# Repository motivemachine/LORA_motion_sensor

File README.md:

# LoRa Motion sensor
These are the kicad PCB and software files for the LoRa motion sensor, a wireless proximity alarm using the RCWL-0516 sensor and SX1278 radio. PCB designed in Kicad 5.1. The cache should contain all custom footprints. Handheld receiver design coming soon.

### Dependencies
Only dependency is the LoRa radio library by [Sandeep Mistry](https://github.com/sandeepmistry/arduino-LoRa), included in _/firmware/lib/_

### Software usage
Software was created and compiled with PlatformIO, but is usable by any arduino compatible IDE by compiling the program located in _/firmware/src_ as an arduino pro mini 3.3v/8mhz. Upload is done over ISP header. Be careful that programming signals are 3.3 volts, as the LoRa radio is not 5v tolerant.

### Using the device
Simply turn it on and place in an area you'd like to monitor. Choke points are best, such as near a gate, pathway, doorway or vehicle. The sensor works by detecting a phase change in it's 3Ghz oscillator and waking up the processor and radio, then sending the packet 'MOT' via LoRa radio protocol, along with packet and radio ID number.

Sensor range is about 20-30ft out the front and back, and less to the sides. Range seems somewhat dependent on size and speed of the object (dog, man, car, etc.), and whether or not the object is moving across or toward/away from the sensor. Sensor is immune to changes in heat or light, and can 'see' through non-conductive objects. It detects movement of conductive objects, be they people, animal or metal vehicle, and sometimes large amounts of tree leaves. Beware if placing near large leafy things in the wind.

The best documentation on the function and use of this sensor can be found here: (https://github.com/jdesbonnet/RCWL-0516)

The only critical part of placing it is near metal or another sensor. Any metal closer than about 2" to the sensor will cause it to go off constantly, and the sensors will interfere with each other closer than about 10feet(~3meters)

Testing is still ongoing, but the device is mostly feature complete. Sleep modes on the radio and ATmega are getting about two weeks (depending on number of wakeups) on a single 18650 battery.  

### Still todo

- [ ] program CRC and collision detection functions
- [ ] write functions for setting destination and local HEX address with switches or solder jumpers
- [ ] update and test boards with low-battery alert functions
- [x] upload platformio files
- [x] upload .pdf of schematic
- [ ] generate and upload a proper BOM

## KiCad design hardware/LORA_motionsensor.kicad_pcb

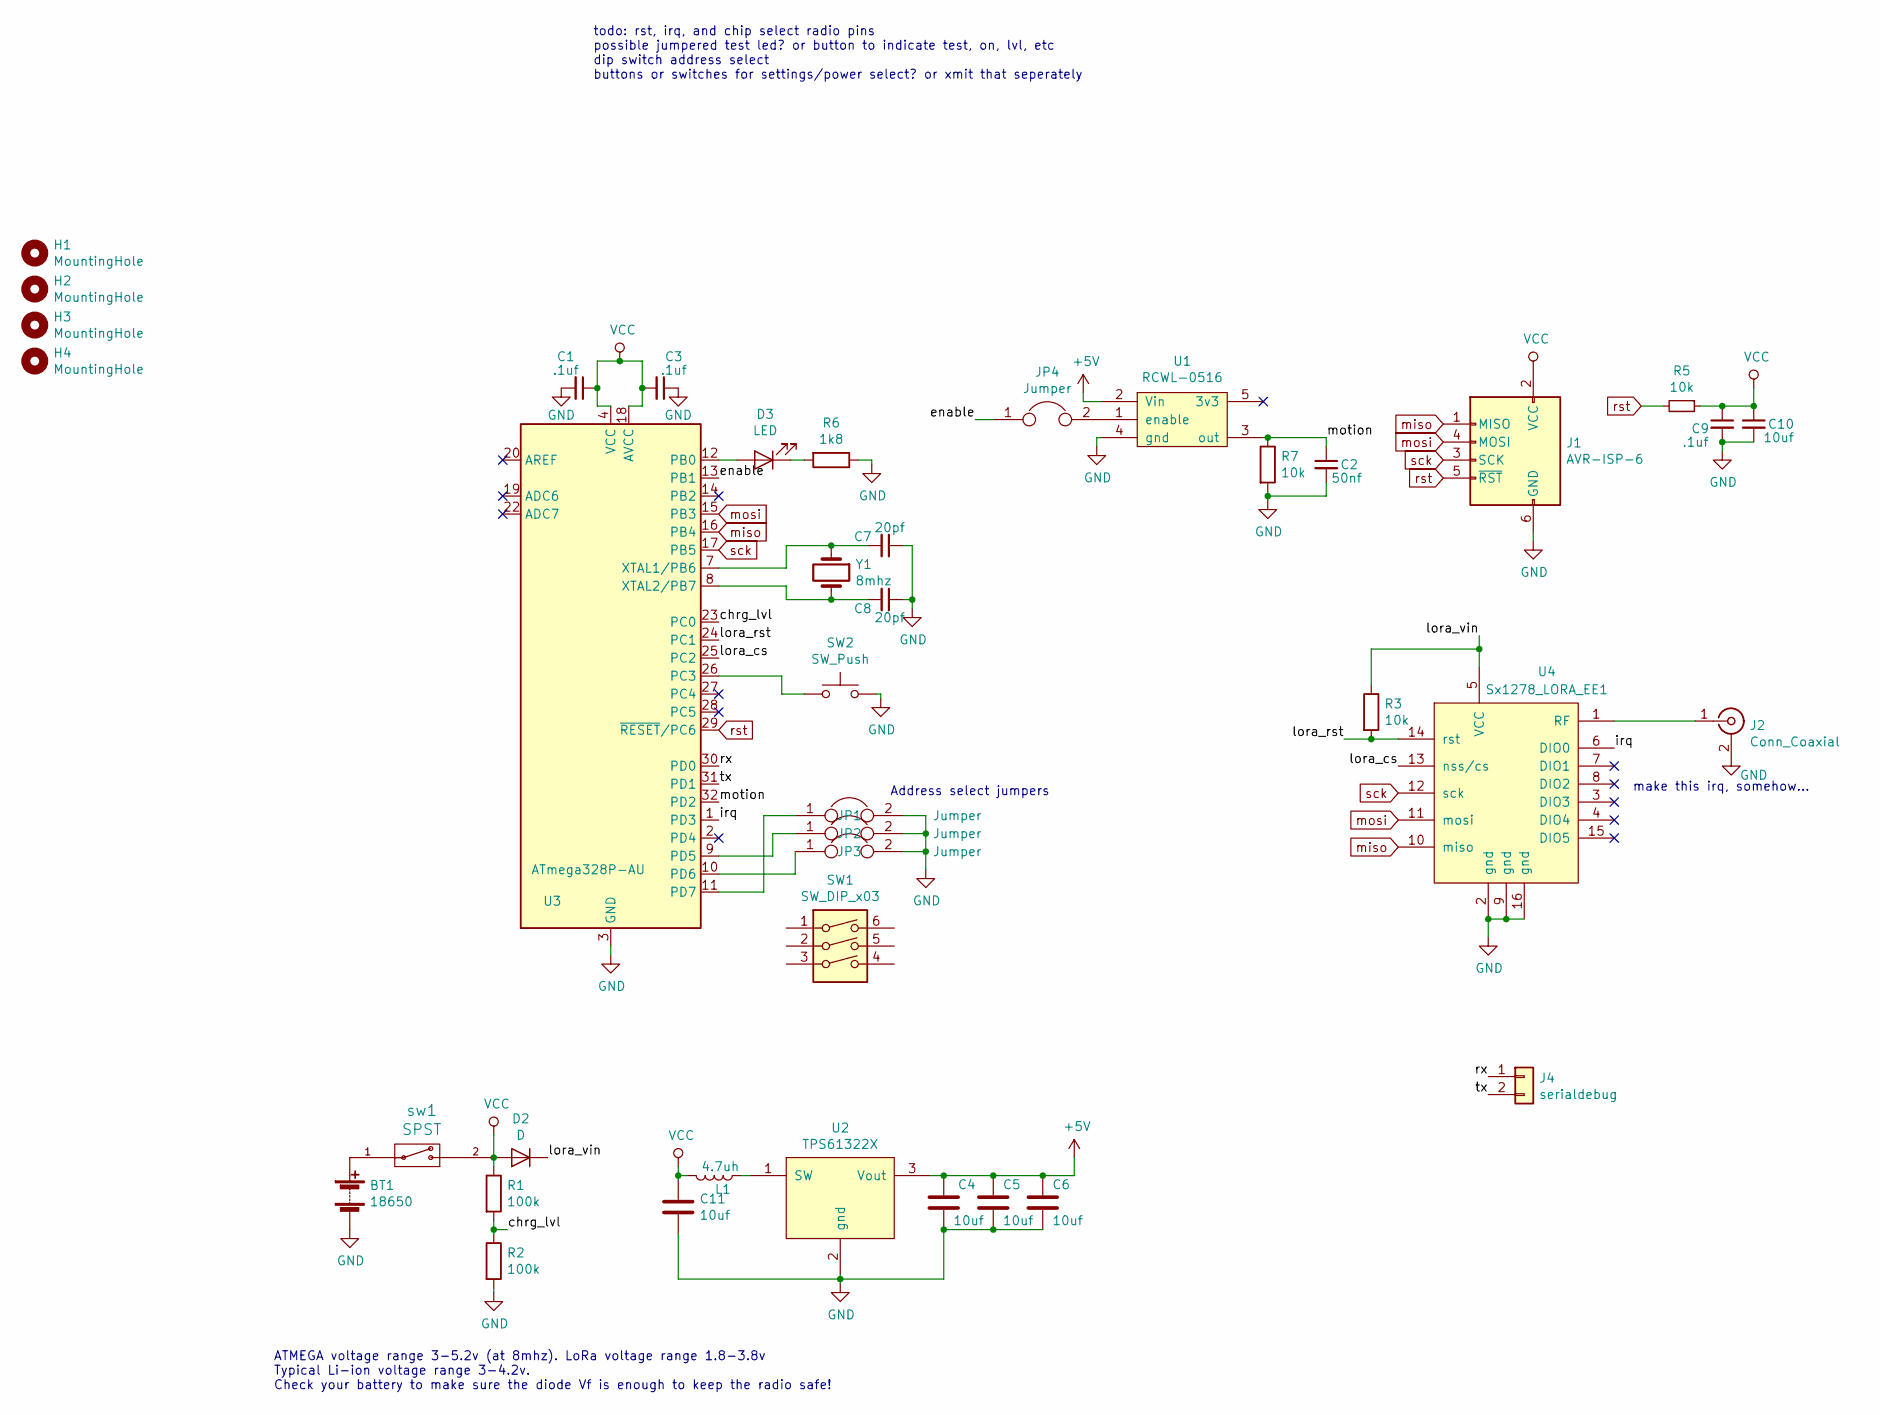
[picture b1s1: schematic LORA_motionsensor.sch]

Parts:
BT1: 18650; 18650_Single_Holder
C1, C3, C9: .1uf; C_0805_2012Metric
C2: 50nf; C_0805_2012Metric
C4, C5, C6, C10, C11: 10uf; C_0805_2012Metric
C7, C8: 20pf; C_0805_2012Metric
D2: D; D_1806_4516Metric
D3: LED; LED_0805_2012Metric
H1, H2, H3, H4: MountingHole; MountingHole_2.2mm_M2
J1: AVR-ISP-6; PinHeader_2x03_P2.54mm_Vertical
J2: Conn_Coaxial; SMA_edgelaunch_SMD
J4: serialdebug; PinHeader_1x02_P2.54mm_Vertical
JP1, JP2, JP3, JP4: Jumper; solder_jumper
L1: 4.7uh; L_0805_HandSoldering
R1, R2: 100k; R_0805_2012Metric
R3, R5, R7: 10k; R_0805_2012Metric
R6: 1k8; R_0805_2012Metric
SW1: SW_DIP_x03; SW_SPDT_slide_lowprofile
SW2: SW_Push; SW_Push_SPST_NO_Alps_SKRK
U1: RCWL-0516
U2: TPS61322X; SOT-23-5
U3: ATmega328P-AU; TQFP-32_7x7mm_P0.8mm
U4: Sx1278_LORA_EE1; LORA_SX1278_Module
Y1: 8mhz; XTAL_SMD_Standard
sw1: SPST; SW_SPDT_slide_lowprofile

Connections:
+5V: C4.1, C5.1, C6.1, U1.2 (Vin), U2.3 (Vout)
/chrg_lvl: R1.2, R2.1, U3.23 (PC0)
/enable: JP4.1, U3.13 (PB1)
/irq: U3.1 (PD3), U4.6 (DIO0)
/lora_cs: U3.25 (PC2), U4.13 (nss/cs)
/lora_rst: R3.2, U3.24 (PC1), U4.14 (rst)
/lora_vin: D2.1 (K), R3.1, U4.5 (VCC)
/motion: C2.1, R7.1, U1.3 (out), U3.32 (PD2)
/rx: J4.1, U3.30 (PD0)
/tx: J4.2, U3.31 (PD1)
GND: BT1.2 (-), C1.2, C2.2, C3.1, C4.2, C5.2, C6.2, C7.1, C8.1, C9.2, C10.2, C11.2, J1.6 (GND), J2.2 (Ext), JP1.2, JP2.2, JP3.2, R2.2, R6.1, R7.2, SW2.2, U1.4 (gnd), U2.2 (gnd), U3.3 (GND), U3.5 (GND), U3.21 (GND), U4.2 (gnd), U4.9 (gnd), U4.16 (gnd)
unnamed: BT1.1 (+), sw1.1
unnamed: C7.2, U3.7 (XTAL1/PB6), Y1.1
unnamed: C8.2, U3.8 (XTAL2/PB7), Y1.2
unnamed: D3.1 (K), R6.2
unnamed: D3.2 (A), U3.12 (PB0)
unnamed: J2.1 (In), U4.1 (RF)
unnamed: JP1.1, U3.11 (PD7)
unnamed: JP2.1, U3.9 (PD5)
unnamed: JP3.1, U3.10 (PD6)
unnamed: JP4.2, U1.1 (enable)
unnamed: L1.1, U2.1 (SW)
unnamed: SW2.1, U3.26 (PC3)
VCC: C1.1, C3.2, C9.1, C10.1, C11.1, D2.2 (A), J1.2 (VCC), L1.2, R1.1, R5.1, U3.4 (VCC), U3.6 (VCC), U3.18 (AVCC), sw1.2
miso: J1.1 (MISO), U3.16 (PB4), U4.10 (miso)
mosi: J1.4 (MOSI), U3.15 (PB3), U4.11 (mosi)
rst: J1.5 (~RST), R5.2, U3.29 (~RESET~/PC6)
sck: J1.3 (SCK), U3.17 (PB5), U4.12 (sck)

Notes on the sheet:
todo: rst, irq, and chip select radio pins possible jumpered test led? or button to indicate test, on, lvl, etc dip switch address select buttons or switches for settings/power select? or xmit that seperately
make this irq, somehow...
ATMEGA voltage range 3-5.2v (at 8mhz). LoRa voltage range 1.8-3.8v Typical Li-ion voltage range 3-4.2v. Check your battery to make sure the diode Vf is enough to keep the radio safe!
Address select jumpers

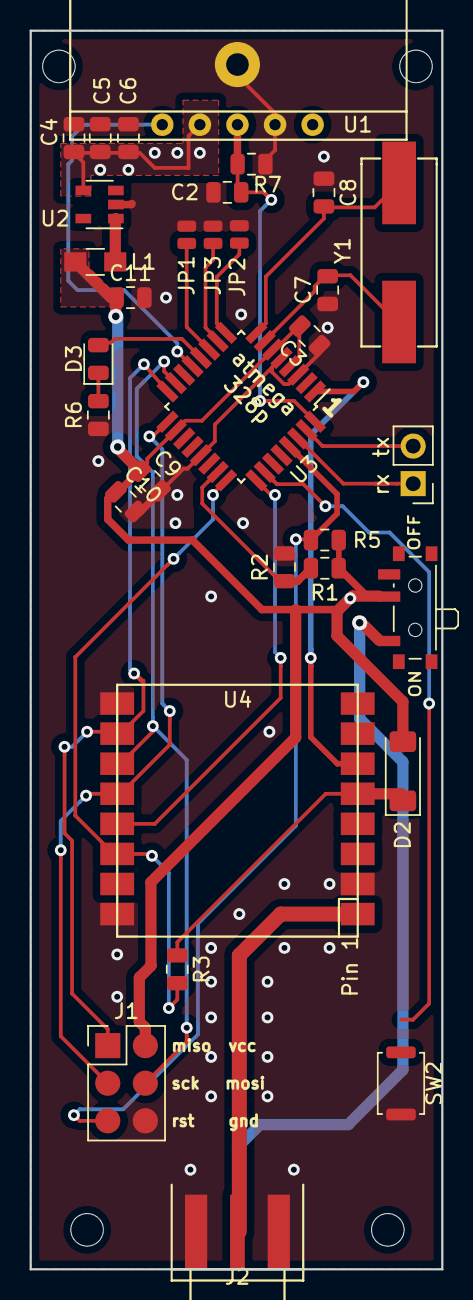
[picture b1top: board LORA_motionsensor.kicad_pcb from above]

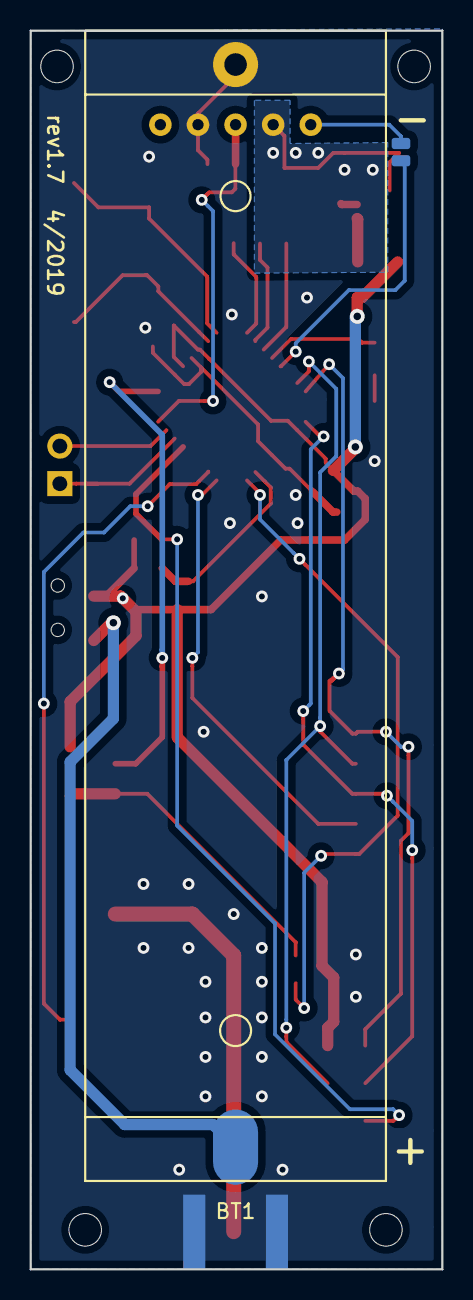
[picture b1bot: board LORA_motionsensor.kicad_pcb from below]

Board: 2 copper layers, 27.8 x 83.7 mm, 38 parts (2 on the bottom side), 28 nets.

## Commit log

2019-05-21 uploading kicad files
2019-05-21 Add LICENSE
2019-05-21 add readme.md
2019-05-21 add lora library
2019-05-28 add .pdf schematic
2019-06-02 added battery test functions
